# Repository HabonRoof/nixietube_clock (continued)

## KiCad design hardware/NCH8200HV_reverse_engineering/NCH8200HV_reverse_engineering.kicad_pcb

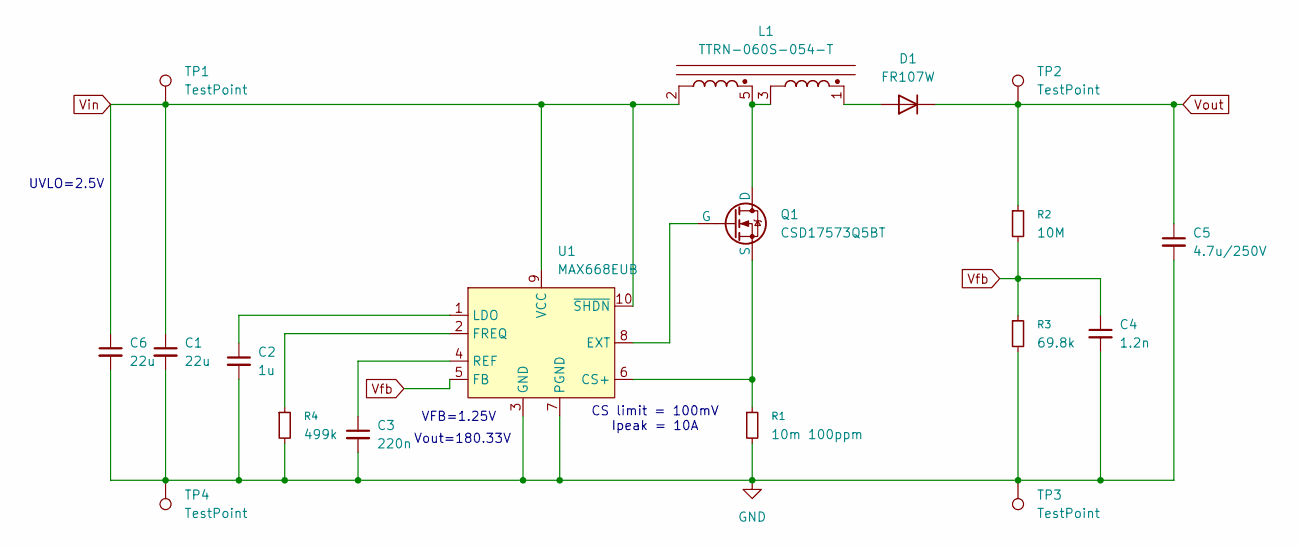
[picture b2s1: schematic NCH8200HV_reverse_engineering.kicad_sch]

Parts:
C1, C6: 22u; C_0805_2012Metric; LCSC PN C45783
C2: 1u; C_0603_1608Metric; LCSC PN C15849
C3: 220n; C_0603_1608Metric; LCSC PN C21120
C4: 1.2n; C_0603_1608Metric; LCSC PN C68659
C5: 4.7u/250V; C_Elec_8x10.2; LCSC PN C88691
D1: FR107W; D_SOD-123F; LCSC PN C108820
L1: TTRN-060S-054-T; EFD6.5_Transformer
Q1: CSD17573Q5BT; PQFN-8-EP_6x5mm_P1.27mm_Generic; LCSC PN C2868471
R1: 10m 100ppm; R_0805_2012Metric; LCSC PN C723457
R2: 10M; R_0603_1608Metric; LCSC PN C7250
R3: 69.8k; R_0603_1608Metric; LCSC PN C23098
R4: 499k; R_0603_1608Metric; LCSC PN C26751
TP1, TP2, TP3, TP4: TestPoint; TestPoint_THTPad_D2.0mm_Drill1.0mm
U1: MAX668EUB; MSOP-10_3x3mm_P0.5mm; LCSC PN C143564

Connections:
GND: C1.2, C2.2, C3.2, C4.2, C5.2, C6.2, R1.2, R3.2, R4.2, TP3.1, TP4.1, U1.3 (GND), U1.7 (PGND)
unnamed: D1.2 (A), L1.1
unnamed: L1.3, L1.5, Q1.5 (D)
unnamed: Q1.4 (G), U1.8 (EXT)
unnamed: Q1.1 (S), R1.1, U1.6 (CS+)
unnamed: R4.1, U1.2 (FREQ)
unnamed: C2.1, U1.1 (LDO)
unnamed: C3.1, U1.4 (REF)
Vfb: C4.1, R2.2, R3.1, U1.5 (FB)
Vin: C1.1, C6.1, L1.2, TP1.1, U1.9 (VCC), U1.10 (~SHDN)
Vout: C5.1, D1.1 (K), R2.1, TP2.1

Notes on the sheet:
UVLO=2.5V
VFB=1.25V
CS limit = 100mV Ipeak = 10A
Vout=180.33V

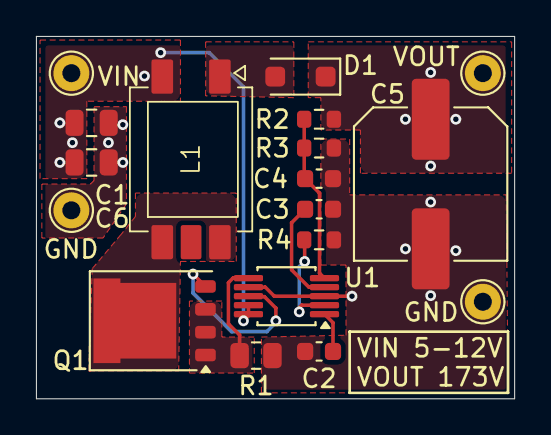
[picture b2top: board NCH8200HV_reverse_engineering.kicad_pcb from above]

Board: 2 copper layers, 26.6 x 20.1 mm, 18 parts (0 on the bottom side), 11 nets.

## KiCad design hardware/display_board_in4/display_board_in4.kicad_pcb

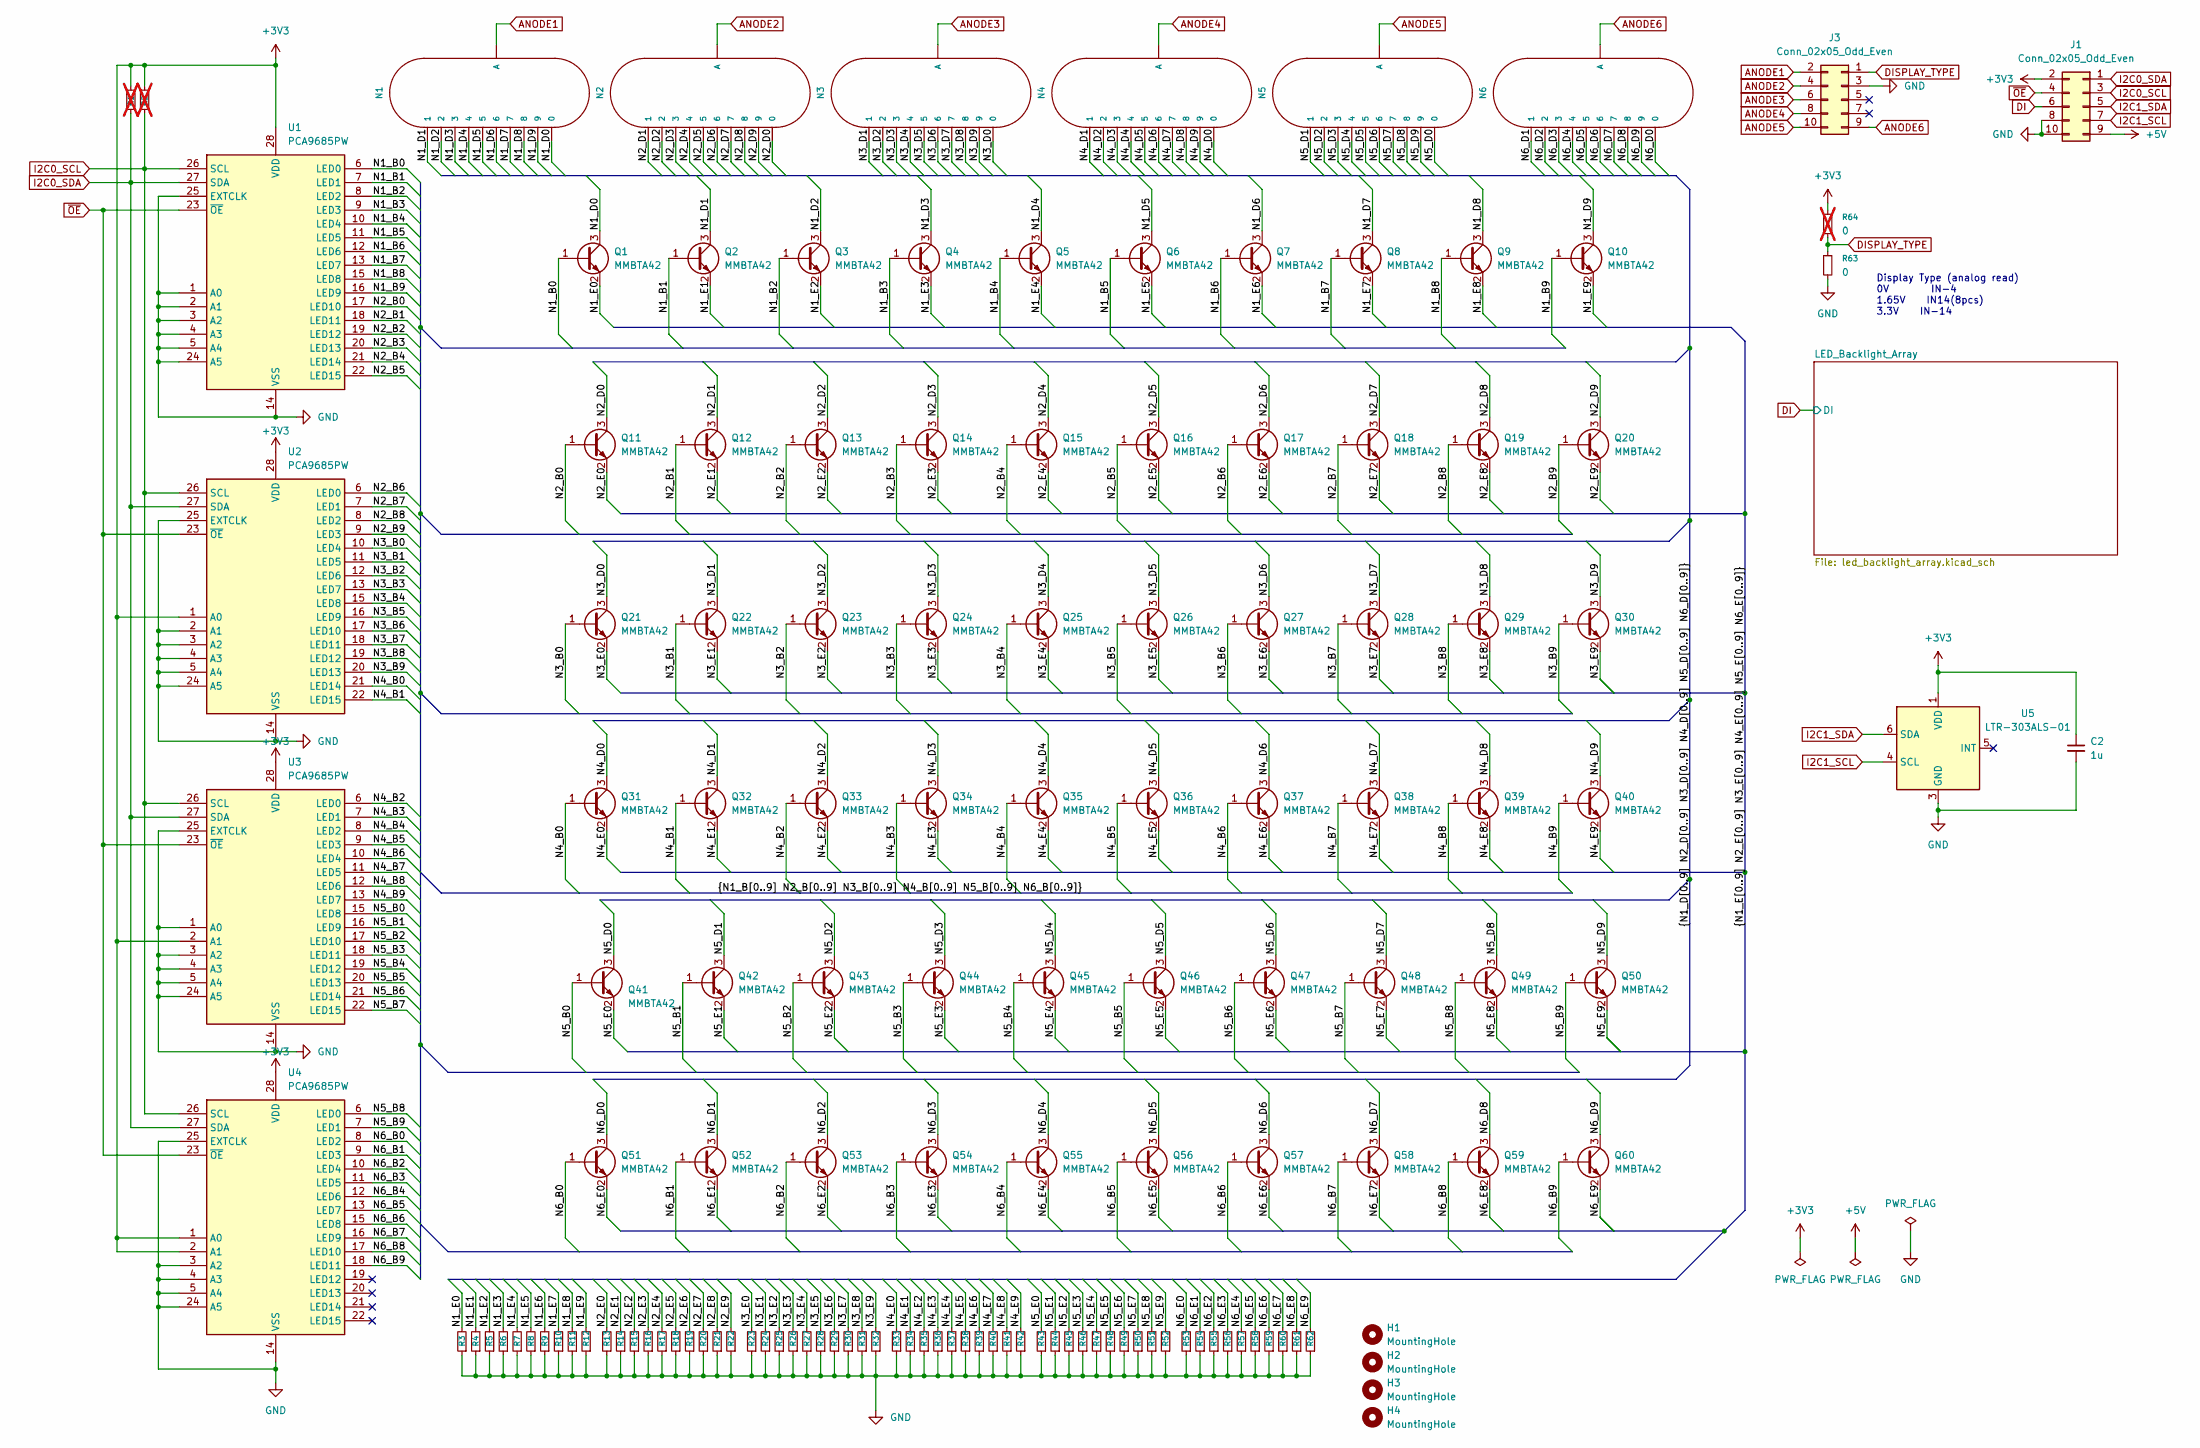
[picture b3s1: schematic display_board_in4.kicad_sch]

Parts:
C2: 1u; C_0603_1608Metric; LCSC PN C15849
H1, H2, H3, H4: MountingHole; MountingHole_3.2mm_M3_DIN965
J1, J3: Conn_02x05_Odd_Even; PinSocket_2x05_P2.00mm_Vertical_SMD; LCSC PN C22373873
N1, N2, N3, N4, N5, N6: IN-4; nixies-us-IN-4-DSUB
Q1, Q2, Q3, Q4, Q5, Q6, Q7, Q8, Q9, Q10, Q11, Q12, Q13, Q14, Q15, Q16, Q17, Q18, Q19, Q20, Q21, Q22, Q23, Q24, Q25, Q26, Q27, Q28, Q29, Q30, Q31, Q32, Q33, Q34, Q35, Q36, Q37, Q38, Q39, Q40, Q41, Q42, Q43, Q44, Q45, Q46, Q47, Q48, Q49, Q50, Q51, Q52, Q53, Q54, Q55, Q56, Q57, Q58, Q59, Q60: MMBTA42; SOT-23; LCSC PN C94389
R1, R2: 2.2k; R_0603_1608Metric; LCSC PN C4190; not fitted
R3, R4, R5, R6, R7, R8, R9, R10, R11, R12, R13, R14, R15, R16, R17, R18, R19, R20, R21, R22, R23, R24, R25, R26, R27, R28, R29, R30, R31, R32, R33, R34, R35, R36, R37, R38, R39, R40, R41, R42, R43, R44, R45, R46, R47, R48, R49, R50, R51, R52, R53, R54, R55, R56, R57, R58, R59, R60, R61, R62: 1k; R_0603_1608Metric; LCSC PN C21190
R63: 0; R_0603_1608Metric; LCSC PN C21189
R64: 0; R_0603_1608Metric; not fitted
U1, U2, U3, U4: PCA9685PW; TSSOP-28_4.4x9.7mm_P0.65mm; LCSC PN C2678753
U5: LTR-303ALS-01; Lite-On_LTR-303ALS-01; LCSC PN C364577

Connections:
+3V3: C2.1, J1.2, R1.1, R2.1, R64.1, U1.28 (VDD), U2.1 (A0), U2.28 (VDD), U3.2 (A1), U3.28 (VDD), U4.1 (A0), U4.2 (A1), U4.28 (VDD), U5.1 (VDD)
+5V: J1.9; also elsewhere on the board
/N1_B0: Q1.1 (B), U1.6 (LED0)
/N1_B1: Q2.1 (B), U1.7 (LED1)
/N1_B2: Q3.1 (B), U1.8 (LED2)
/N1_B3: Q4.1 (B), U1.9 (LED3)
/N1_B4: Q5.1 (B), U1.10 (LED4)
/N1_B5: Q6.1 (B), U1.11 (LED5)
/N1_B6: Q7.1 (B), U1.12 (LED6)
/N1_B7: Q8.1 (B), U1.13 (LED7)
/N1_B8: Q9.1 (B), U1.15 (LED8)
/N1_B9: Q10.1 (B), U1.16 (LED9)
/N1_D0: N1.0, Q1.3 (C)
/N1_D1: N1.1, Q2.3 (C)
/N1_D2: N1.2, Q3.3 (C)
/N1_D3: N1.3, Q4.3 (C)
/N1_D4: N1.4, Q5.3 (C)
/N1_D5: N1.5, Q6.3 (C)
/N1_D6: N1.6, Q7.3 (C)
/N1_D7: N1.7, Q8.3 (C)
/N1_D8: N1.8, Q9.3 (C)
/N1_D9: N1.9, Q10.3 (C)
/N1_E0: Q1.2 (E), R3.2
/N1_E1: Q2.2 (E), R4.2
/N1_E2: Q3.2 (E), R5.2
/N1_E3: Q4.2 (E), R6.2
/N1_E4: Q5.2 (E), R7.2
/N1_E5: Q6.2 (E), R8.2
/N1_E6: Q7.2 (E), R9.2
/N1_E7: Q8.2 (E), R10.2
/N1_E8: Q9.2 (E), R11.2
/N1_E9: Q10.2 (E), R12.2
/N2_B0: Q11.1 (B), U1.17 (LED10)
/N2_B1: Q12.1 (B), U1.18 (LED11)
/N2_B2: Q13.1 (B), U1.19 (LED12)
/N2_B3: Q14.1 (B), U1.20 (LED13)
/N2_B4: Q15.1 (B), U1.21 (LED14)
/N2_B5: Q16.1 (B), U1.22 (LED15)
/N2_B6: Q17.1 (B), U2.6 (LED0)
/N2_B7: Q18.1 (B), U2.7 (LED1)
/N2_B8: Q19.1 (B), U2.8 (LED2)
/N2_B9: Q20.1 (B), U2.9 (LED3)
/N2_D0: N2.0, Q11.3 (C)
/N2_D1: N2.1, Q12.3 (C)
/N2_D2: N2.2, Q13.3 (C)
/N2_D3: N2.3, Q14.3 (C)
/N2_D4: N2.4, Q15.3 (C)
/N2_D5: N2.5, Q16.3 (C)
/N2_D6: N2.6, Q17.3 (C)
/N2_D7: N2.7, Q18.3 (C)
/N2_D8: N2.8, Q19.3 (C)
/N2_D9: N2.9, Q20.3 (C)
/N2_E0: Q11.2 (E), R13.2
/N2_E1: Q12.2 (E), R14.2
/N2_E2: Q13.2 (E), R15.2
/N2_E3: Q14.2 (E), R16.2
/N2_E4: Q15.2 (E), R17.2
/N2_E5: Q16.2 (E), R18.2
/N2_E6: Q17.2 (E), R19.2
/N2_E7: Q18.2 (E), R20.2
/N2_E8: Q19.2 (E), R21.2
/N2_E9: Q20.2 (E), R22.2
/N3_B0: Q21.1 (B), U2.10 (LED4)
/N3_B1: Q22.1 (B), U2.11 (LED5)
/N3_B2: Q23.1 (B), U2.12 (LED6)
/N3_B3: Q24.1 (B), U2.13 (LED7)
/N3_B4: Q25.1 (B), U2.15 (LED8)
/N3_B5: Q26.1 (B), U2.16 (LED9)
/N3_B6: Q27.1 (B), U2.17 (LED10)
/N3_B7: Q28.1 (B), U2.18 (LED11)
/N3_B8: Q29.1 (B), U2.19 (LED12)
/N3_B9: Q30.1 (B), U2.20 (LED13)
/N3_D0: N3.0, Q21.3 (C)
/N3_D1: N3.1, Q22.3 (C)
/N3_D2: N3.2, Q23.3 (C)
/N3_D3: N3.3, Q24.3 (C)
/N3_D4: N3.4, Q25.3 (C)
/N3_D5: N3.5, Q26.3 (C)
/N3_D6: N3.6, Q27.3 (C)
/N3_D7: N3.7, Q28.3 (C)
/N3_D8: N3.8, Q29.3 (C)
/N3_D9: N3.9, Q30.3 (C)
/N3_E0: Q21.2 (E), R23.2
/N3_E1: Q22.2 (E), R24.2
/N3_E2: Q23.2 (E), R25.2
/N3_E3: Q24.2 (E), R26.2
/N3_E4: Q25.2 (E), R27.2
/N3_E5: Q26.2 (E), R28.2
/N3_E6: Q27.2 (E), R29.2
/N3_E7: Q28.2 (E), R30.2
/N3_E8: Q29.2 (E), R31.2
/N3_E9: Q30.2 (E), R32.2
/N4_B0: Q31.1 (B), U2.21 (LED14)
/N4_B1: Q32.1 (B), U2.22 (LED15)
/N4_B2: Q33.1 (B), U3.6 (LED0)
/N4_B3: Q34.1 (B), U3.7 (LED1)
/N4_B4: Q35.1 (B), U3.8 (LED2)
/N4_B5: Q36.1 (B), U3.9 (LED3)
/N4_B6: Q37.1 (B), U3.10 (LED4)
/N4_B7: Q38.1 (B), U3.11 (LED5)
/N4_B8: Q39.1 (B), U3.12 (LED6)
/N4_B9: Q40.1 (B), U3.13 (LED7)
/N4_D0: N4.0, Q31.3 (C)
/N4_D1: N4.1, Q32.3 (C)
/N4_D2: N4.2, Q33.3 (C)
/N4_D3: N4.3, Q34.3 (C)
/N4_D4: N4.4, Q35.3 (C)
/N4_D5: N4.5, Q36.3 (C)
/N4_D6: N4.6, Q37.3 (C)
/N4_D7: N4.7, Q38.3 (C)
/N4_D8: N4.8, Q39.3 (C)
/N4_D9: N4.9, Q40.3 (C)
/N4_E0: Q31.2 (E), R33.2
/N4_E1: Q32.2 (E), R34.2
/N4_E2: Q33.2 (E), R35.2
/N4_E3: Q34.2 (E), R36.2
/N4_E4: Q35.2 (E), R37.2
/N4_E5: Q36.2 (E), R38.2
/N4_E6: Q37.2 (E), R39.2
/N4_E7: Q38.2 (E), R40.2
/N4_E8: Q39.2 (E), R41.2
/N4_E9: Q40.2 (E), R42.2
/N5_B0: Q41.1 (B), U3.15 (LED8)
/N5_B1: Q42.1 (B), U3.16 (LED9)
/N5_B2: Q43.1 (B), U3.17 (LED10)
/N5_B3: Q44.1 (B), U3.18 (LED11)
/N5_B4: Q45.1 (B), U3.19 (LED12)
/N5_B5: Q46.1 (B), U3.20 (LED13)
/N5_B6: Q47.1 (B), U3.21 (LED14)
/N5_B7: Q48.1 (B), U3.22 (LED15)
/N5_B8: Q49.1 (B), U4.6 (LED0)
/N5_B9: Q50.1 (B), U4.7 (LED1)
/N5_D0: N5.0, Q41.3 (C)
/N5_D1: N5.1, Q42.3 (C)
/N5_D2: N5.2, Q43.3 (C)
/N5_D3: N5.3, Q44.3 (C)
/N5_D4: N5.4, Q45.3 (C)
/N5_D5: N5.5, Q46.3 (C)
/N5_D6: N5.6, Q47.3 (C)
/N5_D7: N5.7, Q48.3 (C)
/N5_D8: N5.8, Q49.3 (C)
/N5_D9: N5.9, Q50.3 (C)
/N5_E0: Q41.2 (E), R43.2
/N5_E1: Q42.2 (E), R44.2
/N5_E2: Q43.2 (E), R45.2
/N5_E3: Q44.2 (E), R46.2
/N5_E4: Q45.2 (E), R47.2
/N5_E5: Q46.2 (E), R48.2
/N5_E6: Q47.2 (E), R49.2
/N5_E7: Q48.2 (E), R50.2
/N5_E8: Q49.2 (E), R51.2
/N5_E9: Q50.2 (E), R52.2
/N6_B0: Q51.1 (B), U4.8 (LED2)
/N6_B1: Q52.1 (B), U4.9 (LED3)
/N6_B2: Q53.1 (B), U4.10 (LED4)
/N6_B3: Q54.1 (B), U4.11 (LED5)
/N6_B4: Q55.1 (B), U4.12 (LED6)
/N6_B5: Q56.1 (B), U4.13 (LED7)
/N6_B6: Q57.1 (B), U4.15 (LED8)
/N6_B7: Q58.1 (B), U4.16 (LED9)
/N6_B8: Q59.1 (B), U4.17 (LED10)
/N6_B9: Q60.1 (B), U4.18 (LED11)
/N6_D0: N6.0, Q51.3 (C)
/N6_D1: N6.1, Q52.3 (C)
/N6_D2: N6.2, Q53.3 (C)
/N6_D3: N6.3, Q54.3 (C)
/N6_D4: N6.4, Q55.3 (C)
/N6_D5: N6.5, Q56.3 (C)
/N6_D6: N6.6, Q57.3 (C)
/N6_D7: N6.7, Q58.3 (C)
/N6_D8: N6.8, Q59.3 (C)
/N6_D9: N6.9, Q60.3 (C)
/N6_E0: Q51.2 (E), R53.2
/N6_E1: Q52.2 (E), R54.2
/N6_E2: Q53.2 (E), R55.2
/N6_E3: Q54.2 (E), R56.2
/N6_E4: Q55.2 (E), R57.2
/N6_E5: Q56.2 (E), R58.2
/N6_E6: Q57.2 (E), R59.2
/N6_E7: Q58.2 (E), R60.2
/N6_E8: Q59.2 (E), R61.2
/N6_E9: Q60.2 (E), R62.2
ANODE1: J3.2, N1.A3 (A)
ANODE2: J3.4, N2.A3 (A)
ANODE3: J3.6, N3.A3 (A)
ANODE4: J3.8, N4.A3 (A)
ANODE5: J3.10, N5.A3 (A)
ANODE6: J3.9, N6.A3 (A)
DI: J1.6; also elsewhere on the board
DISPLAY_TYPE: J3.1, R63.1, R64.2
GND: C2.2, J1.8, J1.10, J3.3, R3.1, R4.1, R5.1, R6.1, R7.1, R8.1, R9.1, R10.1, R11.1, R12.1, R13.1, R14.1, R15.1, R16.1, R17.1, R18.1, R19.1, R20.1, R21.1, R22.1, R23.1, R24.1, R25.1, R26.1, R27.1, R28.1, R29.1, R30.1, R31.1, R32.1, R33.1, R34.1, R35.1, R36.1, R37.1, R38.1, R39.1, R40.1, R41.1, R42.1, R43.1, R44.1, R45.1, R46.1, R47.1, R48.1, R49.1, R50.1, R51.1, R52.1, R53.1, R54.1, R55.1, R56.1, R57.1, R58.1, R59.1, R60.1, R61.1, R62.1, R63.2, U1.1 (A0), U1.2 (A1), U1.3 (A2), U1.4 (A3), U1.5 (A4), U1.14 (VSS), U1.24 (A5), U1.25 (EXTCLK), U2.2 (A1), U2.3 (A2), U2.4 (A3), U2.5 (A4), U2.14 (VSS), U2.24 (A5), U2.25 (EXTCLK), U3.1 (A0), U3.3 (A2), U3.4 (A3), U3.5 (A4), U3.14 (VSS), U3.24 (A5), U3.25 (EXTCLK), U4.3 (A2), U4.4 (A3), U4.5 (A4), U4.14 (VSS), U4.24 (A5), U4.25 (EXTCLK), U5.3 (GND); also elsewhere on the board
I2C0_SCL: J1.3, R2.2, U1.26 (SCL), U2.26 (SCL), U3.26 (SCL), U4.26 (SCL)
I2C0_SDA: J1.1, R1.2, U1.27 (SDA), U2.27 (SDA), U3.27 (SDA), U4.27 (SDA)
I2C1_SCL: J1.7, U5.4 (SCL)
I2C1_SDA: J1.5, U5.6 (SDA)
~OE: J1.4, U1.23 (~OE), U2.23 (~OE), U3.23 (~OE), U4.23 (~OE)

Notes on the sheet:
Display Type (analog read) 0V IN-4 1.65V IN14(8pcs) 3.3V IN-14

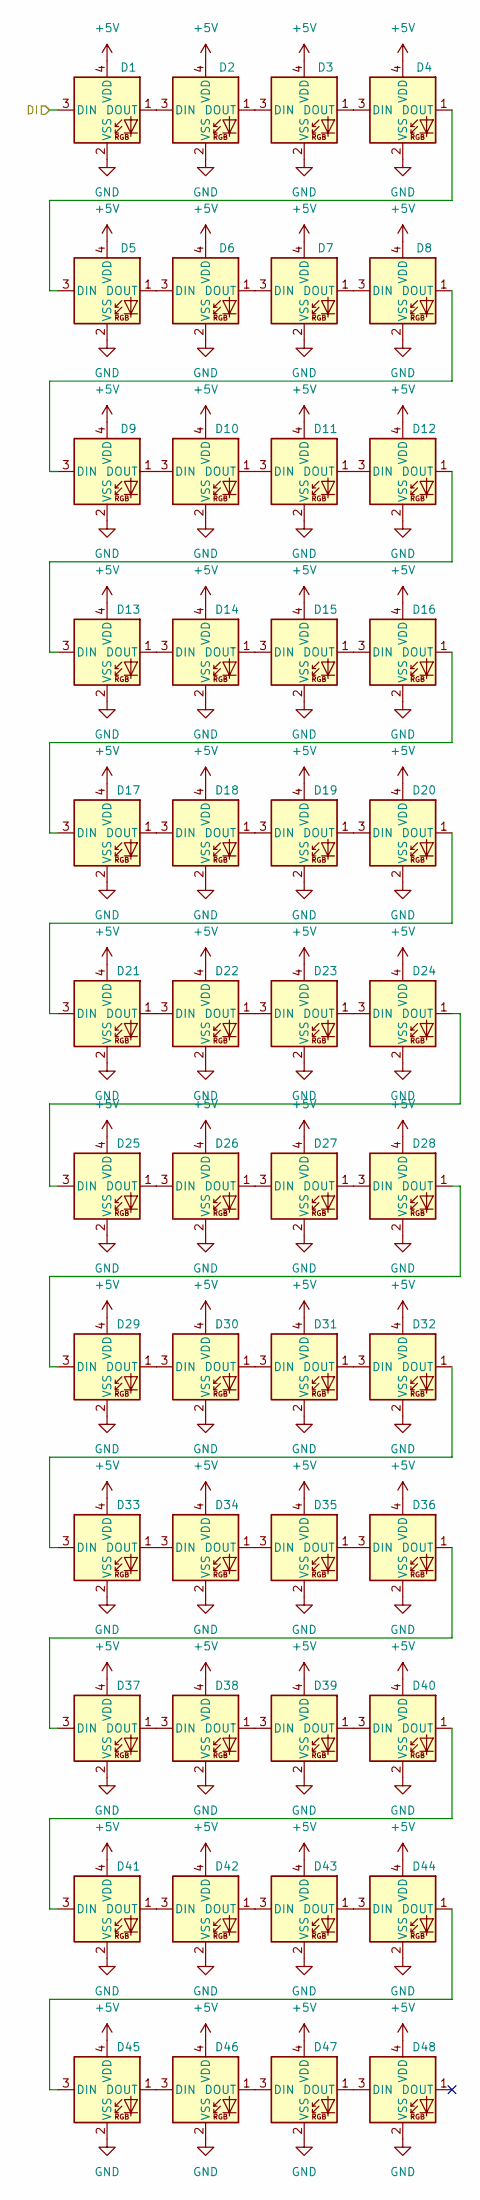
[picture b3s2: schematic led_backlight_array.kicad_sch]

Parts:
D1, D2, D3, D4, D5, D6, D7, D8, D9, D10, D11, D12, D13, D14, D15, D16, D17, D18, D19, D20, D21, D22, D23, D24, D25, D26, D27, D28, D29, D30, D31, D32, D33, D34, D35, D36, D37, D38, D39, D40, D41, D42, D43, D44, D45, D46, D47, D48: WS2812B-2020; LED_WS2812B-2020_PLCC4_2.0x2.0mm; LCSC PN C965555

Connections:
+5V: D1.4 (VDD), D2.4 (VDD), D3.4 (VDD), D4.4 (VDD), D5.4 (VDD), D6.4 (VDD), D7.4 (VDD), D8.4 (VDD), D9.4 (VDD), D10.4 (VDD), D11.4 (VDD), D12.4 (VDD), D13.4 (VDD), D14.4 (VDD), D15.4 (VDD), D16.4 (VDD), D17.4 (VDD), D18.4 (VDD), D19.4 (VDD), D20.4 (VDD), D21.4 (VDD), D22.4 (VDD), D23.4 (VDD), D24.4 (VDD), D25.4 (VDD), D26.4 (VDD), D27.4 (VDD), D28.4 (VDD), D29.4 (VDD), D30.4 (VDD), D31.4 (VDD), D32.4 (VDD), D33.4 (VDD), D34.4 (VDD), D35.4 (VDD), D36.4 (VDD), D37.4 (VDD), D38.4 (VDD), D39.4 (VDD), D40.4 (VDD), D41.4 (VDD), D42.4 (VDD), D43.4 (VDD), D44.4 (VDD), D45.4 (VDD), D46.4 (VDD), D47.4 (VDD), D48.4 (VDD); also elsewhere on the board
DI: D1.3 (DIN); also elsewhere on the board
GND: D1.2 (VSS), D2.2 (VSS), D3.2 (VSS), D4.2 (VSS), D5.2 (VSS), D6.2 (VSS), D7.2 (VSS), D8.2 (VSS), D9.2 (VSS), D10.2 (VSS), D11.2 (VSS), D12.2 (VSS), D13.2 (VSS), D14.2 (VSS), D15.2 (VSS), D16.2 (VSS), D17.2 (VSS), D18.2 (VSS), D19.2 (VSS), D20.2 (VSS), D21.2 (VSS), D22.2 (VSS), D23.2 (VSS), D24.2 (VSS), D25.2 (VSS), D26.2 (VSS), D27.2 (VSS), D28.2 (VSS), D29.2 (VSS), D30.2 (VSS), D31.2 (VSS), D32.2 (VSS), D33.2 (VSS), D34.2 (VSS), D35.2 (VSS), D36.2 (VSS), D37.2 (VSS), D38.2 (VSS), D39.2 (VSS), D40.2 (VSS), D41.2 (VSS), D42.2 (VSS), D43.2 (VSS), D44.2 (VSS), D45.2 (VSS), D46.2 (VSS), D47.2 (VSS), D48.2 (VSS); also elsewhere on the board
unnamed: D1.1 (DOUT), D2.3 (DIN)
unnamed: D2.1 (DOUT), D3.3 (DIN)
unnamed: D3.1 (DOUT), D4.3 (DIN)
unnamed: D4.1 (DOUT), D5.3 (DIN)
unnamed: D5.1 (DOUT), D6.3 (DIN)
unnamed: D6.1 (DOUT), D7.3 (DIN)
unnamed: D7.1 (DOUT), D8.3 (DIN)
unnamed: D8.1 (DOUT), D9.3 (DIN)
unnamed: D9.1 (DOUT), D10.3 (DIN)
unnamed: D10.1 (DOUT), D11.3 (DIN)
unnamed: D11.1 (DOUT), D12.3 (DIN)
unnamed: D12.1 (DOUT), D13.3 (DIN)
unnamed: D13.1 (DOUT), D14.3 (DIN)
unnamed: D14.1 (DOUT), D15.3 (DIN)
unnamed: D15.1 (DOUT), D16.3 (DIN)
unnamed: D16.1 (DOUT), D17.3 (DIN)
unnamed: D17.1 (DOUT), D18.3 (DIN)
unnamed: D18.1 (DOUT), D19.3 (DIN)
unnamed: D19.1 (DOUT), D20.3 (DIN)
unnamed: D20.1 (DOUT), D21.3 (DIN)
unnamed: D21.1 (DOUT), D22.3 (DIN)
unnamed: D22.1 (DOUT), D23.3 (DIN)
unnamed: D23.1 (DOUT), D24.3 (DIN)
unnamed: D24.1 (DOUT), D25.3 (DIN)
unnamed: D25.1 (DOUT), D26.3 (DIN)
unnamed: D26.1 (DOUT), D27.3 (DIN)
unnamed: D27.1 (DOUT), D28.3 (DIN)
unnamed: D28.1 (DOUT), D29.3 (DIN)
unnamed: D29.1 (DOUT), D30.3 (DIN)
unnamed: D30.1 (DOUT), D31.3 (DIN)
unnamed: D31.1 (DOUT), D32.3 (DIN)
unnamed: D32.1 (DOUT), D33.3 (DIN)
unnamed: D33.1 (DOUT), D34.3 (DIN)
unnamed: D34.1 (DOUT), D35.3 (DIN)
unnamed: D35.1 (DOUT), D36.3 (DIN)
unnamed: D36.1 (DOUT), D37.3 (DIN)
unnamed: D37.1 (DOUT), D38.3 (DIN)
unnamed: D38.1 (DOUT), D39.3 (DIN)
unnamed: D39.1 (DOUT), D40.3 (DIN)
unnamed: D40.1 (DOUT), D41.3 (DIN)
unnamed: D41.1 (DOUT), D42.3 (DIN)
unnamed: D42.1 (DOUT), D43.3 (DIN)
unnamed: D43.1 (DOUT), D44.3 (DIN)
unnamed: D44.1 (DOUT), D45.3 (DIN)
unnamed: D45.1 (DOUT), D46.3 (DIN)
unnamed: D46.1 (DOUT), D47.3 (DIN)
unnamed: D47.1 (DOUT), D48.3 (DIN)

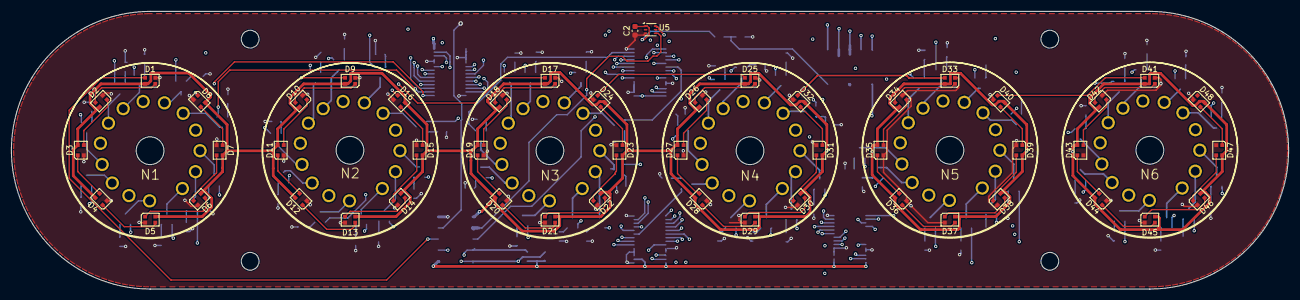
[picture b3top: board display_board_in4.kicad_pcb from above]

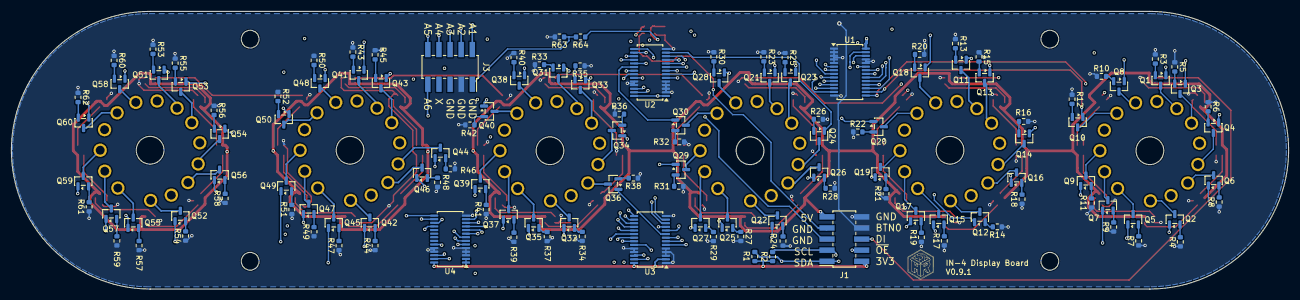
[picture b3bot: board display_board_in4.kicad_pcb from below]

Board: 4 copper layers, 230.0 x 50.0 mm, 190 parts (130 on the bottom side), 243 nets.

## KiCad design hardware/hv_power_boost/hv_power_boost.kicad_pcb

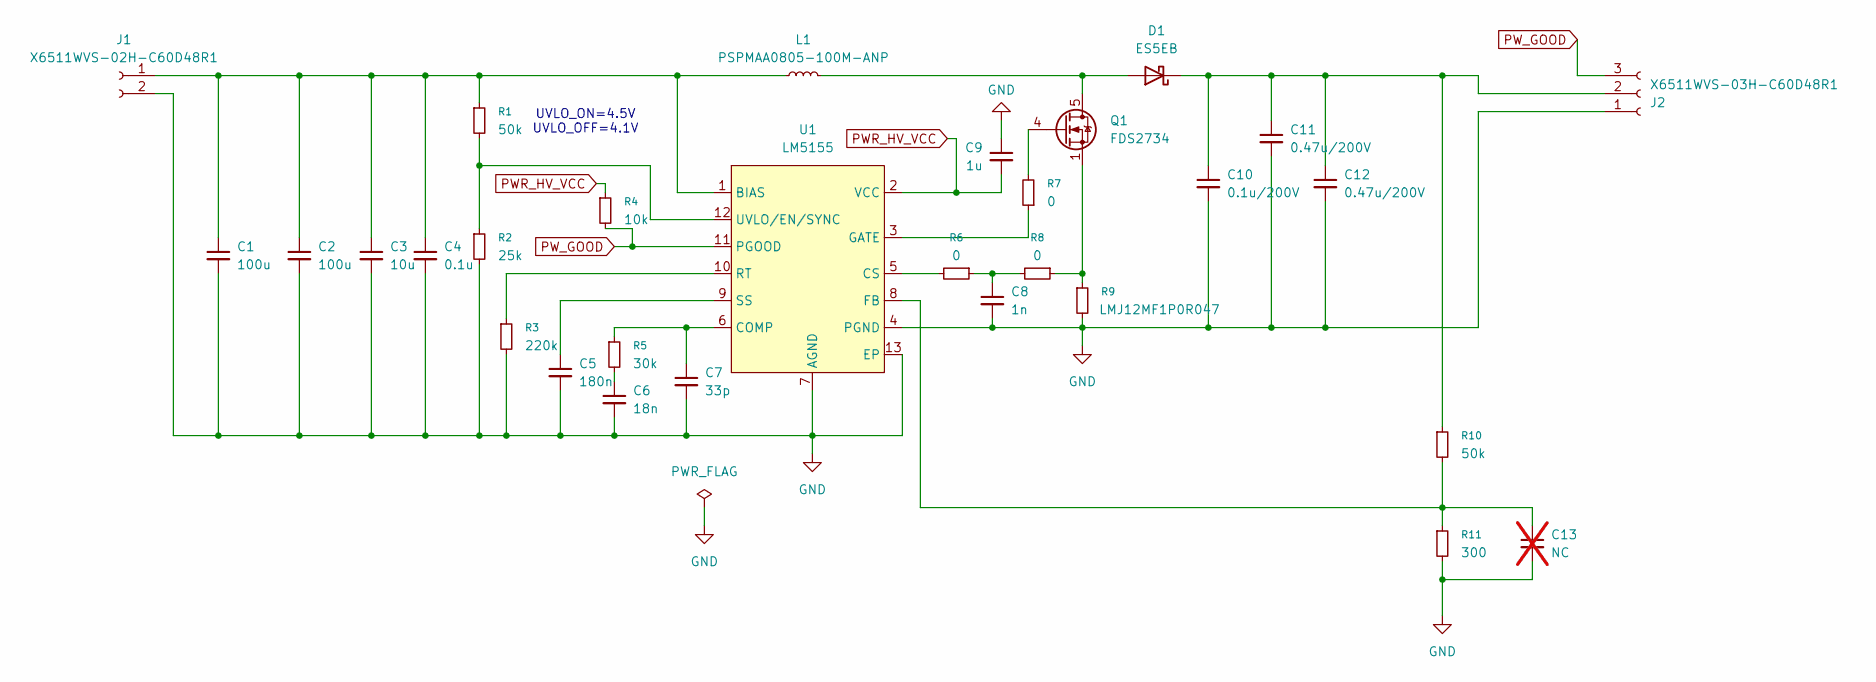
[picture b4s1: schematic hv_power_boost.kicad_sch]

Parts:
C1, C2: 100u; C_1206_3216Metric; LCSC PN C15008
C3: 10u; C_0603_1608Metric; LCSC PN C109453
C4: 0.1u; C_0603_1608Metric; LCSC PN C36911391
C5: 180n; C_0603_1608Metric; LCSC PN C519442
C6: 18n; C_0603_1608Metric; LCSC PN C519551
C7: 33p; C_0603_1608Metric; LCSC PN C107047
C8: 1n; C_0603_1608Metric; LCSC PN C100040
C9: 1u; C_0603_1608Metric; LCSC PN C106248
C10: 0.1u/200V; C_1206_3216Metric; LCSC PN C113894
C11, C12: 0.47u/200V; C_1206_3216Metric; LCSC PN C725802
C13: NC; C_0603_1608Metric; not fitted
D1: ES5EB; D_SMB; LCSC PN C437860
J1: X6511WVS-02H-C60D48R1; PinHeader_1x02_P2.54mm_Vertical_SMD_Pin1Right; LCSC PN C2883799
J2: X6511WVS-03H-C60D48R1; PinHeader_1x03_P2.54mm_Vertical_SMD_Pin1Right; LCSC PN C780061
L1: PSPMAA0805-100M-ANP; PowerInductor_8mmx8.5mm; LCSC PN C2962885
Q1: FDS2734; SOIC-8_3.9x4.9mm_P1.27mm; LCSC PN C606022
R1, R10: 50k; R_0603_1608Metric; LCSC PN C304067
R2: 25k; R_0603_1608Metric; LCSC PN C2828637
R3: 220k; R_0603_1608Metric; LCSC PN C217882
R4: 10k; R_0603_1608Metric; LCSC PN C217687
R5: 30k; R_0603_1608Metric; LCSC PN C2828685
R6, R7, R8: 0; R_0603_1608Metric; LCSC PN C304185
R9: LMJ12MF1P0R047; R_1206_3216Metric; LCSC PN C5121701
R11: 300; R_0603_1608Metric; LCSC PN C217952
U1: LM5155; WSON-12-1EP_3x2mm_P0.5mm_EP1x2.65; LCSC PN C545416

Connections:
GND: C1.2, C2.2, C3.2, C4.2, C5.2, C6.2, C7.2, C8.2, C9.1, C10.2, C11.2, C12.2, C13.2, J1.2, J2.1, R2.2, R3.2, R9.2, R11.2, U1.4 (PGND), U1.7 (AGND), U1.13 (EP)
unnamed: C6.1, R5.2
unnamed: C8.1, R6.1, R8.2
unnamed: D1.2 (A), L1.2, Q1.5 (D), Q1.6 (D), Q1.7 (D), Q1.8 (D)
unnamed: C10.1, C11.1, C12.1, D1.1 (K), J2.2, R10.1
unnamed: C1.1, C2.1, C3.1, C4.1, J1.1, L1.1, R1.1, U1.1 (BIAS)
unnamed: Q1.4 (G), R7.2
unnamed: Q1.1 (S), Q1.2 (S), Q1.3 (S), R8.1, R9.1
unnamed: C7.1, R5.1, U1.6 (COMP)
unnamed: R6.2, U1.5 (CS)
unnamed: C13.1, R10.2, R11.1, U1.8 (FB)
unnamed: R7.1, U1.3 (GATE)
unnamed: R3.1, U1.10 (RT)
unnamed: C5.1, U1.9 (SS)
unnamed: R1.2, R2.1, U1.12 (UVLO/EN/SYNC)
PWR_HV_VCC: C9.2, R4.1, U1.2 (VCC)
PW_GOOD: J2.3, R4.2, U1.11 (PGOOD)

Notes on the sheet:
UVLO_ON=4.5V UVLO_OFF=4.1V

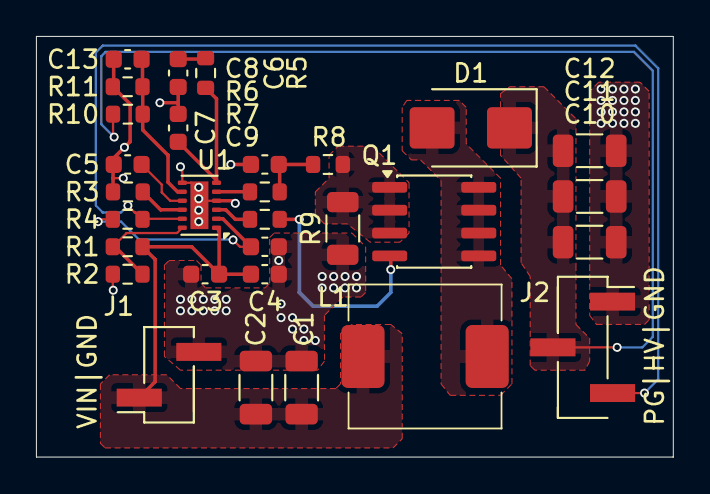
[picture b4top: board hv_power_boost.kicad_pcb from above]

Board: 2 copper layers, 35.4 x 23.4 mm, 30 parts (0 on the bottom side), 17 nets.

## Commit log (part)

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2025-12-15 feat(init): initial commit, RGB led backlight function
2025-12-16 chore(ws2812): change variable naming
2025-12-16 feat(ws2812): change from legacy rtm driver to latest rtm driver
2025-12-16 feat(color): remove oklch color model and using hsv model for more convenient implementation
2026-01-01 refactor(object): refactor the nixie tube object and led object
2026-01-03 refactor(led): refactor led object
2026-01-04 refactor(led): refactor the led backlight implementation
2026-01-04 feat(audio): add new module DFPlayer mini support
2026-01-04 chore(pinout): modify the GPIO pinout for prototype development
2026-01-20 refactor(system): refactor all system architecture for more modulize and clear boundary
2026-01-20 chore(nixie_tube): remove semaphore, the nixie tube should be only accessable by display_daemon
2026-01-20 feat(cli): add simple cli command for project to prepare automation tests and hardware debug
2026-01-21 feat(cli): add ESP32 IDF fw version to cli, support for esp32_s3_devkitc_1 enviorement
2026-01-21 feat(cli): add help and reboot command
2026-01-22 feat(nixie_driver): implement nixie tube driver using PCA9685
2026-01-22 feat(hardware): add kicad design file to repository
2026-01-22 doc(satasheet): add datasheets for design reference
2026-01-22 fix(hardware): correct comment on schematic, change DZ3231 default address to 0x68
2026-01-22 feat(rtc): add ds3231 support, refactor hardware initialize process in SystemController
2026-01-22 refactor(i2c): refactor i2c initialize process, remove redundent code
2026-01-22 doc(readme): update readme for current approach
2026-01-22 doc(pic): update system architecture picture
2026-01-22 feat(web_server): add web server support to setup clock, this is the simple concept verification
2026-01-26 hardware(schematic): update in4 display board current limit resistor to 68kOhm, update pin connector to 2X5 pin, no more GND1 needed, it's non-isloated
2026-01-26 chore(gitignore): update gitignore file
2026-01-26 hardware(sch): update hv boost output capacitor, update connector pinout
2026-01-26 feat(gasgauge): support bq24711 gasgauge driver
2026-01-28 WIP(hardware): in4 display board routing
2026-01-29 feat(monitor): add power monitor support using INA3221
2026-01-29 WIP(hardware): update in-4 display board
2026-01-29 WIP(hardware): in4 display board layout
2026-01-29 WIP(haedware): add TPS62177 buck converter for 3v3 regulation
2026-01-30 WIP(hardware): update main board and mainboard layout
2026-02-02 chore(hardware): complete mainboard layout
2026-02-03 chore(hardware): shrink main board size to lower the PCB price
2026-02-03 chore(hardware): update bom and LCSC SN
2026-04-07 update ignore file types
2026-04-07 hardware(schematic): Update IN-4 schematic and layout
2026-04-07 hardware(schematic): update main control board schematic and layout
2026-04-07 hardware(schematic): update hv boost board compensation value, update design document
2026-04-07 doc(pic): add some debugging waveform
2026-04-07 chore: update battery capacity
2026-04-07 feat: bq25601 charging IC support, implement to charging daemon
2026-04-07 feat: add charger daemon support in cli
2026-04-07 feat(charging): start the daemon in main
2026-04-07 fix(led): fix the number of led to 48
2026-04-07 feat(system): keep system controller stack big enough for growing message type
2026-05-07 doc(datasheet): add new datasheet for new solution
2026-06-03 chore(sch): adjust 3v3, 5v and power switch solutions.
2026-06-09 hardware(sch): update component package to 0402 as most as possable, layout is still need to complete
2026-06-10 hardware(sch): fix CP2102 VBUS connection. This pin should connect to 5V
2026-06-11 fix(nixie): Fix anode scan feature, now the anode will scan at 1kHz, but the cathode only update in 100Hz.
2026-06-14 debug(main): disable I2C modules to debug gasgauge
2026-06-14 fix(gasgauge): extrace gasgauge from display daemon for better isolation and reduce the usage of I2C bus. Add I2CLock in each I2C module to reduce the collision change. Add CLI support for gasgauge r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
2026-06-16 test for doc commit
2026-06-16 fix(daemon): remove ina3221 current measurement feature for cost. Rename power_daemon to power_controller, the function is no longer a daemon, it's only a utility to turn-on/off the switch. Remove so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
2026-06-16 Add pull-up resistor for DS3231 interrupt pin
2026-06-16 fix(compiler): Add library path to compiler
2026-06-16 feat(charger): refactor the charger utility, change deamon to controller. There is no periodic task for charger.
2026-06-16 chore(gasgauge): add switch to enable/disable the daemon for debug purpose
2026-06-17 feat(rtc): first version of driver
2026-06-17 refactor(gasgauge): remove gasgauge daemon and turn it into utility to reduce the CPU usage. Combine the setting_store and system_state to single sourcem use system controller to get the information
2026-06-17 fix(system): fix compile error
2026-06-17 fix(rtc): reset OSF for battery less debug usage
2026-06-17 fix(rtc): change rtc read period to one hour
2026-06-17 hardware(imu): remove imu for more cost effective
2026-06-18 hardware(als): Add ALS sensor LTR-303ALS to detect light, add push button as input.
2026-06-18 feat(als): Add als support for V0.91 version hardware.
2026-06-18 chore(webui): change webUI layout and use native roller for time select, use color wheel and slide bar to select RGB color, live update color and volume settings.
2026-06-18 chore(webUI): Expose led backlight animation in webUI, also add led ogg feature.
2026-06-18 chore(webUI): remove oval color wheel, use small square to preview the color
2026-06-18 fix(led): fix the brightness is not apply for breath effect issue
2026-06-18 fix(webUI): Use local time instead UTC time for setting
2026-06-18 doc: update readme
2026-06-18 hardware(display): fix the rotation of IN-4 tube
2026-06-19 feat(webUI): add track list to webUI, improve DFplayer command
2026-06-20 fix(audio): fix the wrong pin assignment
2026-06-20 chore(audio): remove initialize check for DFPlayer, fix webUI sd track count command to flash file count, not sure why sd file count is not working. Also another thing is the query get more count the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
2026-06-20 chore(debug): remove debug message
2026-06-22 chore(nixie): set nixie tube to maximum brightness
2026-06-22 hardware(display): add button and ALS sensor on display board, align the nixie tube
2026-06-22 refactor(nixie): simplify tube mapping logic for cathodes across PCA9685 chips
2026-06-30 feat(webui): add auto-calibrate feature for RTC time, when refreshing the weboage, it should update the RTC to the local time of mobile device.
2026-06-30 doc(waveform): add tap inductor measurement waveform
2026-06-30 feat(rtc): update webui, remove manual time updating interface add alarm function, set and select audio track on webui
